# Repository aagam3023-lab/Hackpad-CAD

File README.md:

# Hackpad-CAD

3D enclosure and CAD files for my custom Hackpad macropad project.

## Onshape CAD Model

The Hackpad enclosure and assembly were designed in Onshape.

[View the Hackpad Assembly](https://cad.onshape.com/documents/c6913491314a9c061a844068/w/89b42ceb321a141e0c2d2ef8/e/c561864a575fdc102dc74ee5)

## CAD Files

- `Hack pad .step` — Exported 3D CAD model for viewing and further CAD work.

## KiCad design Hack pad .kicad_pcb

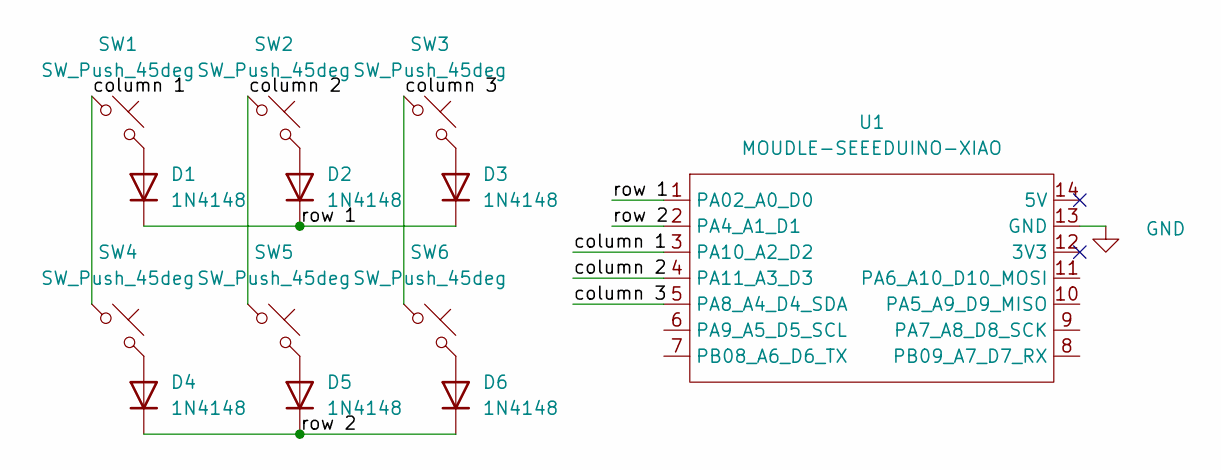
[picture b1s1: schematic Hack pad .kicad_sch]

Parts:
D1, D2, D3, D4, D5, D6: 1N4148; D_DO-35_SOD27_P7.62mm_Horizontal
SW1, SW2, SW3, SW4, SW5, SW6: SW_Push_45deg; SW_Cherry_MX_1.00u_PCB
U1: MOUDLE-SEEEDUINO-XIAO; XIAO-Generic-Hybrid-14P-2.54-21X17.8MM

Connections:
/ENC_L_A: U1.6 (PA9_A5_D5_SCL)
/ENC_L_B: U1.7 (PB08_A6_D6_TX)
/ENC_L_SW: U1.8 (PB09_A7_D7_RX)
/ENC_R_A: U1.9 (PA7_A8_D8_SCK)
/ENC_R_B: U1.10 (PA5_A9_D9_MISO)
/ENC_R_SW: U1.11 (PA6_A10_D10_MOSI)
/column 1: SW1.1, SW4.1, U1.3 (PA10_A2_D2)
/column 2: SW2.1, SW5.1, U1.4 (PA11_A3_D3)
/column 3: SW3.1, SW6.1, U1.5 (PA8_A4_D4_SDA)
/row 1: D1.1 (K), D2.1 (K), D3.1 (K), U1.1 (PA02_A0_D0)
/row 2: D4.1 (K), D5.1 (K), D6.1 (K), U1.2 (PA4_A1_D1)
GND: U1.13 (GND)
unnamed: D1.2 (A), SW1.2
unnamed: D2.2 (A), SW2.2
unnamed: D3.2 (A), SW3.2
unnamed: D4.2 (A), SW4.2
unnamed: D5.2 (A), SW5.2
unnamed: D6.2 (A), SW6.2

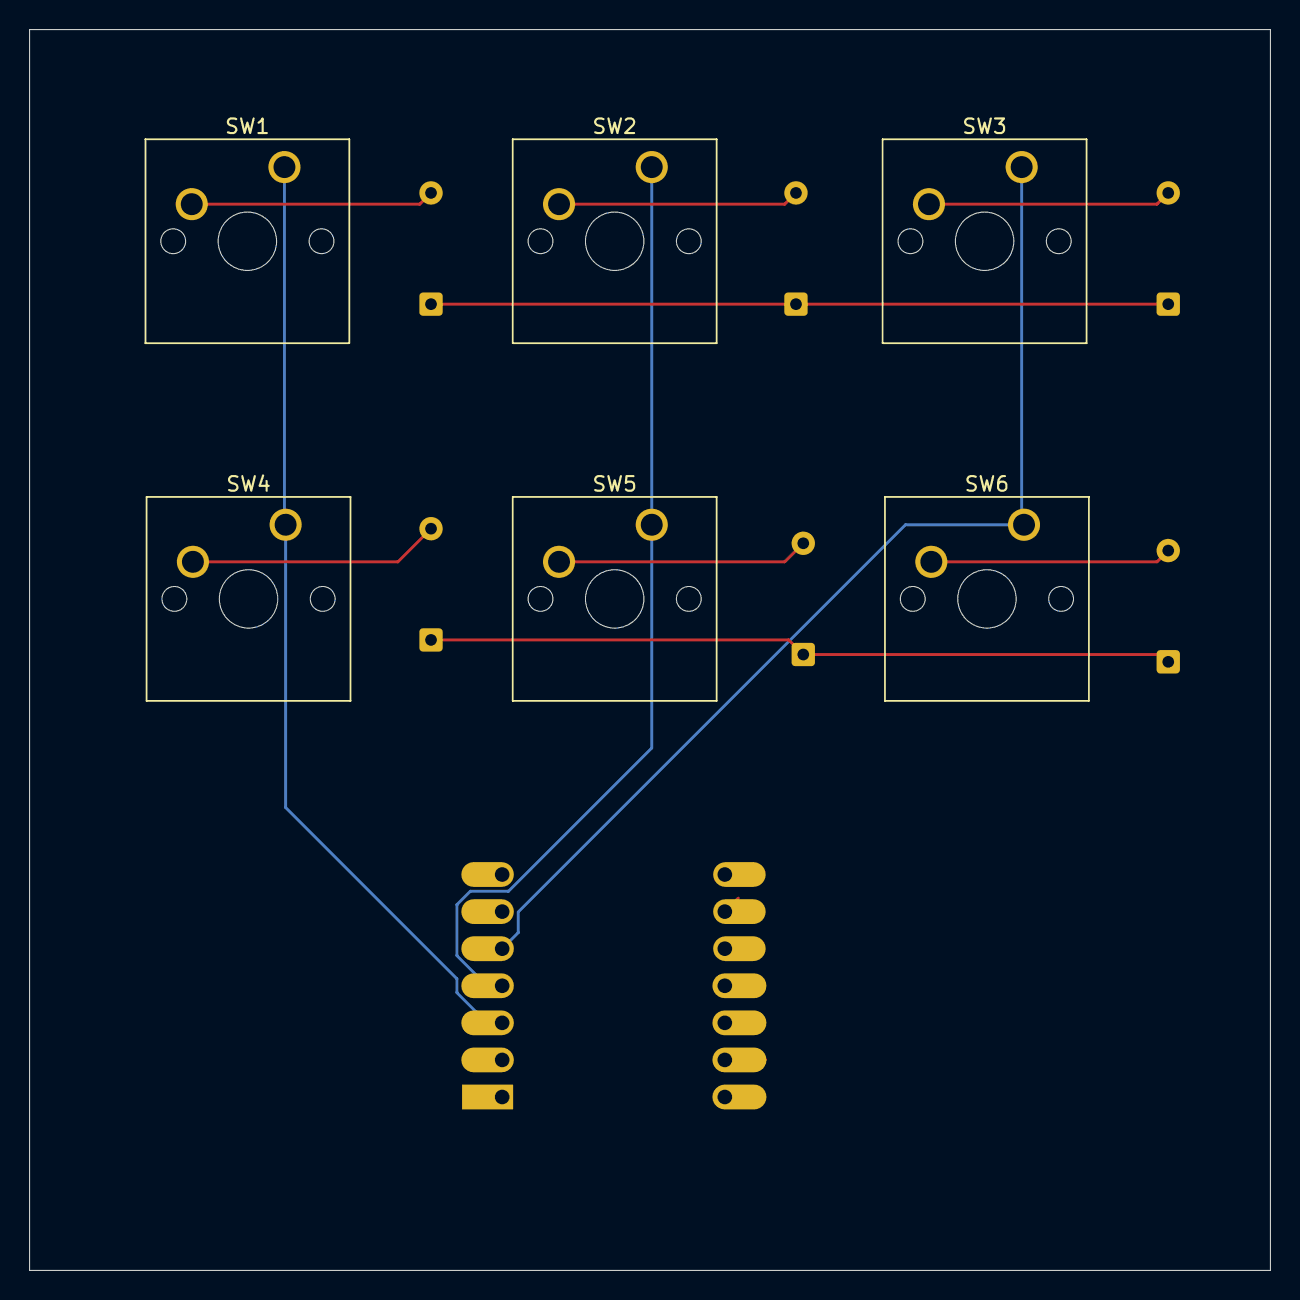
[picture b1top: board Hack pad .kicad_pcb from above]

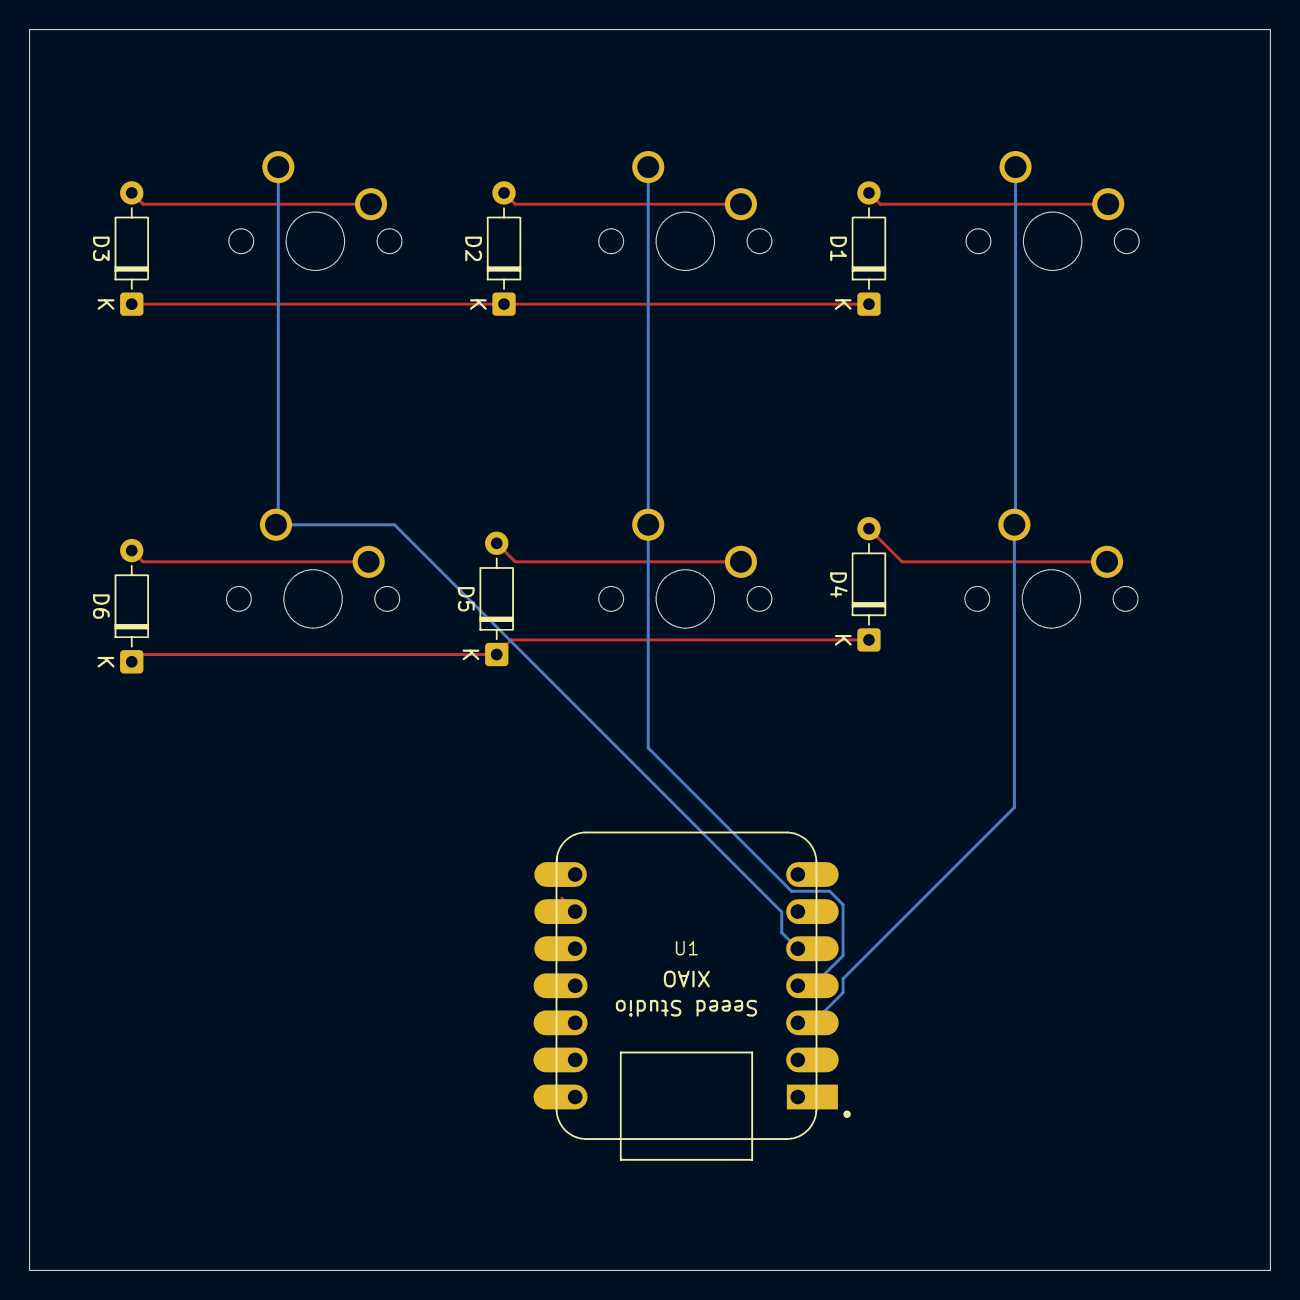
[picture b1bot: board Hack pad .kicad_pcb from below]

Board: 2 copper layers, 85.0 x 85.0 mm, 13 parts (7 on the bottom side), 11 nets.
